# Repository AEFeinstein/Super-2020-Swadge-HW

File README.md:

# Super 2020 Swadge Hardware

This repo contains hardware files for the Super 2020 Barrel and Banana Swadges, as well as the Swadge Programmer and the Swadge Devkit. [KiCad](https://www.kicad-pcb.org/) is used to work with the project files. [Inkscape](https://inkscape.org/) is used to work with the SVG vectors.

The corresponding hardware repository for the Super 2020 Swadge Firmware [can be found here](https://github.com/AEFeinstein/Super-2020-Swadge-FW).

The Barrel and Banana use the same schematic:

View this project on [CADLAB.io](https://cadlab.io/project/1918).

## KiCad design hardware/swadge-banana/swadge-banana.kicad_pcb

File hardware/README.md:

More libraries can be found at https://github.com/kitspace/kicad_footprints

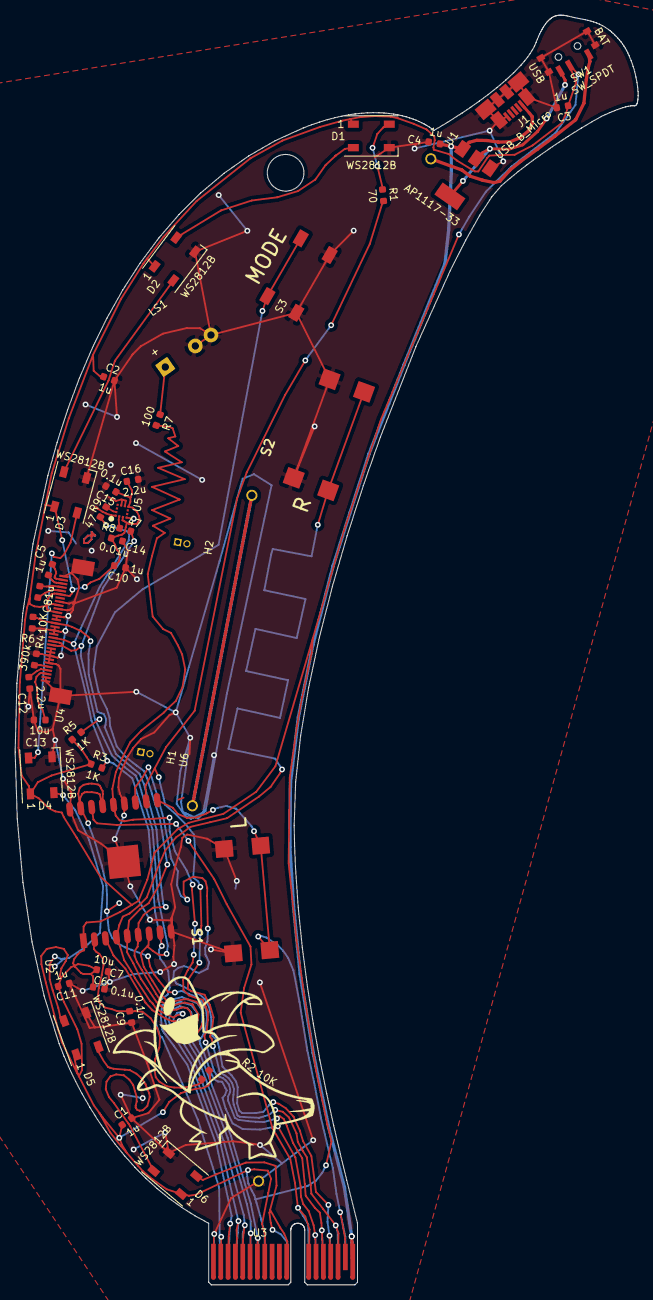
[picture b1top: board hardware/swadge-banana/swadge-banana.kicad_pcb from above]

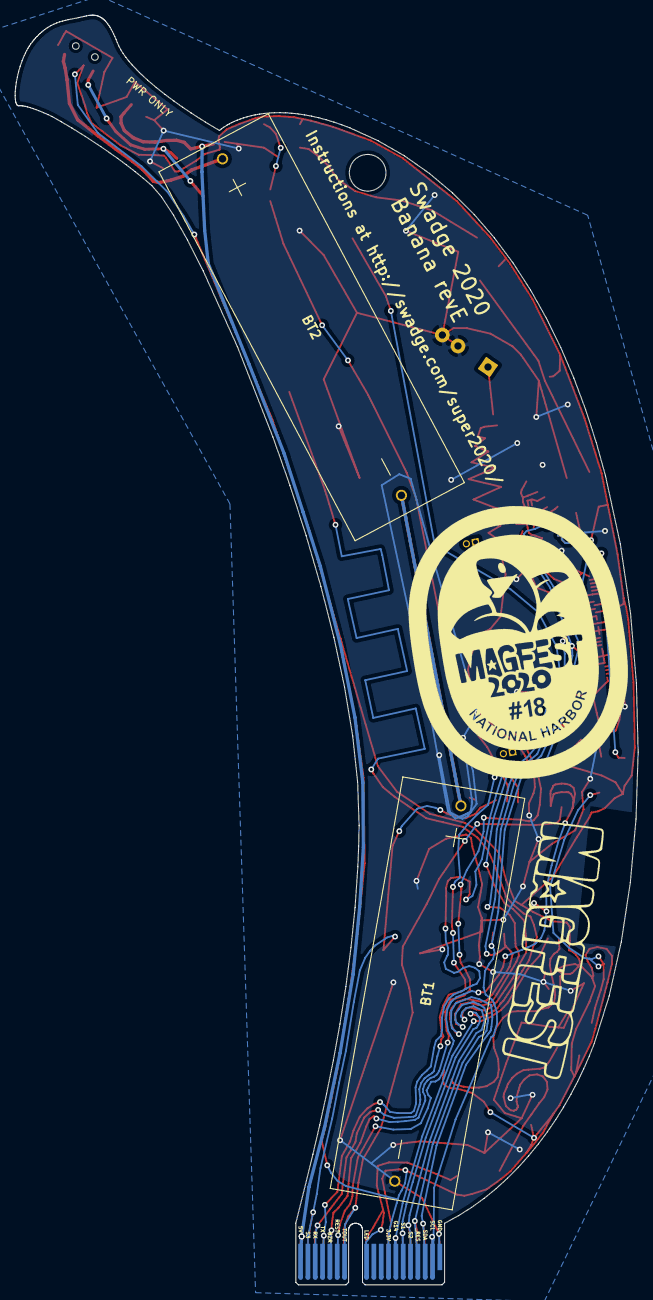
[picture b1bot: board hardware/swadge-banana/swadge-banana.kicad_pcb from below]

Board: 2 copper layers, 85.0 x 173.2 mm, 49 parts (3 on the bottom side), 36 nets.

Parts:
BT1, BT2: Battery; 2460
C1, C2, C3, C4, C5, C8, C10, C11: 1u; C_0603_1608Metric
C6, C13: 10u; C_0603_1608Metric
C7, C9, C15: 0.1u; C_0603_1608Metric
C12, C16: 2.2u; C_0603_1608Metric
C14: 0.01u; C_0603_1608Metric
D1, D2, D3, D4, D5, D6: WS2812B; LED_WS2812B_PLCC4_5.0x5.0mm_P3.2mm
H1: Headband
H2: Headband; NULL
J1: USB_B_Micro; USB_Micro-B_Molex_47346-0001
LS1: Speaker; Buzzer_12x9.5RM7.6
R1: 70; R_0603_1608Metric
R2, R6: 10K; R_0603_1608Metric
R3, R5: 1K; R_0603_1608Metric
R4: 390k; R_0603_1608Metric
R7: 100; R_0603_1608Metric
R8, R9: 47; R_0603_1608Metric
Ref**: Val**; bananaraptor_xl
Ref**#2: Val**; banana-label
S1, S2: B3FS-4002P; B3FS4002P
S3: 4-1437565-2; SW_4-1437565-2
SW1: SW_SPDT; SW_SPDT_PCM12
U1: AP1117-33; SOT-223-3_TabPin2
U2: ESP-13-WROOM-02D; ESP-13-WROOM-02
U3: BUS_PCIexpress
U4: OLED_CONNECTOR; ER-OLED0.96-1.3
U5: QMA6981; QMA6981_2
U6: OLED_DISPLAY; NULL

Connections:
+3V3: C1.1, C2.1, C3.1, C6.2, C7.2, C10.2, C11.2, C14.1, C15.1, C16.1, D1.1, D2.1, D3.1, D4.1, D5.1, D6.1, R2.1, R3.1, R5.1, SW1.2, U2.1, U3.A8, U3.B8, U4.6, U4.9, U4.11, U5.3, U5.7
+5V: C4.1, J1.1, U1.3, U3.A18, U3.B18
ADC_PIN: U2.16, U3.A12, U3.B12
AUD_PWR: U2.3, U3.A7, U3.B7
BZR: R7.2, U2.14, U3.A14, U3.B14
GND: BT1.2, C1.2, C2.2, C3.2, C4.2, C6.1, C7.1, C9.1, C10.1, C11.1, C12.1, C13.1, C14.2, C15.2, C16.2, D1.3, D2.3, D3.3, D4.3, D5.3, D6.3, J1.5, J1.6, LS1.2, R4.1, R6.1, S1.3, S1.4, S2.3, S2.4, S3.3, S3.4, SW1.4, SW1.5, SW1.6, SW1.7, U1.1, U2.9, U2.13, U2.18, U2.PAD, U3.A1, U3.B1, U4.1, U4.8, U4.10, U4.12, U4.13, U4.15, U4.16, U4.17, U4.21, U4.22, U4.23, U4.24, U4.25, U4.29, U4.30, U4.31, U5.1, U5.4, U5.8, U5.9
LED_OUT: D6.2, U3.A11, U3.B11
unnamed: BT1.1, BT2.2
unnamed: BT2.1, SW1.1
unnamed: C5.1, U4.2
unnamed: C5.2, U4.3
unnamed: C8.1, U4.4
unnamed: C8.2, U4.5
unnamed: C9.2, R2.2, U2.2
unnamed: C12.2, U4.27
unnamed: C13.2, U4.28
unnamed: D1.2, D2.4
unnamed: D1.4, R1.1
unnamed: D2.2, D3.4
unnamed: D3.2, D4.4
unnamed: D4.2, D5.4
unnamed: D5.2, D6.4
unnamed: LS1.1, R7.1
unnamed: R4.2, U4.26
unnamed: R8.1, U5.2
unnamed: R9.2, U5.12
unnamed: SW1.3, U1.2
REST: U2.15, U2.17, U3.A13, U3.B13
RX: R1.2, U2.11, U3.A16, U3.B16
SCL: R3.2, R9.1, U2.8, U3.A2, U3.B2, U4.18
SDA: R5.2, R8.2, U2.7, U3.A3, U3.B3, U4.19, U4.20
SW1: S2.1, S2.2, U2.4, U3.A6, U3.B6
SW2: S3.1, S3.2, U2.5, U3.A5, U3.B5
SW3: S1.1, S1.2, U2.10, U3.A17, U3.B17
TX: U2.12, U3.A15, U3.B15
_RES: R6.2, U2.6, U3.A4, U3.B4, U4.14

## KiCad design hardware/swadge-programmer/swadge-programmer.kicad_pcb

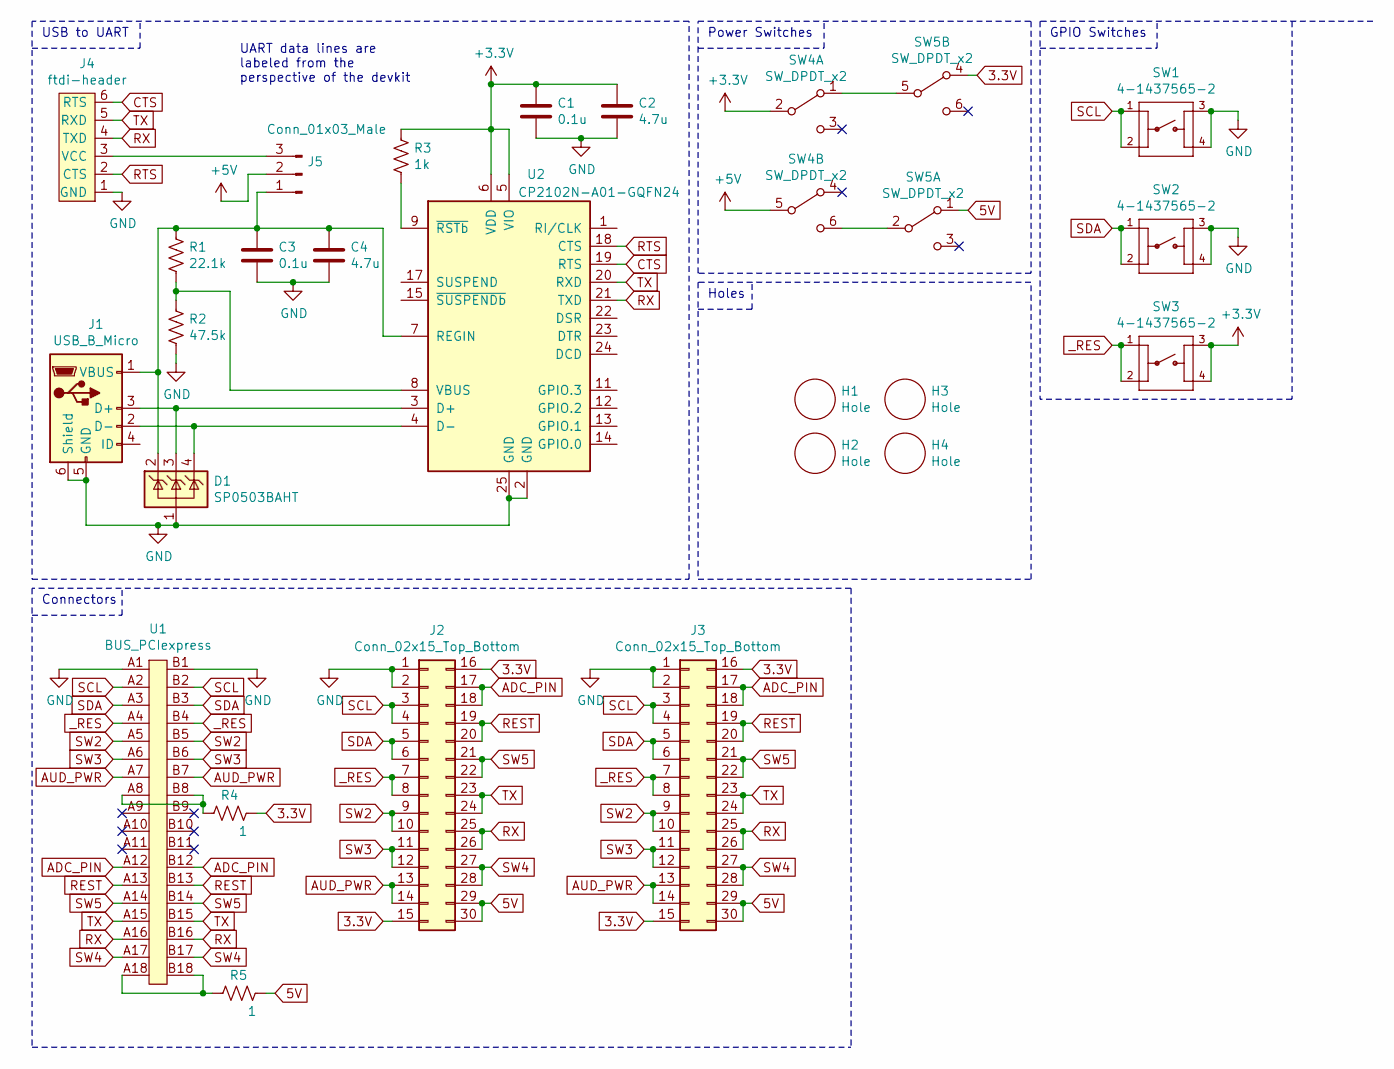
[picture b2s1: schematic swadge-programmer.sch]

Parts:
C1, C3: 0.1u; C_0603_1608Metric; Digikey 1276-1000-1-ND
C2, C4: 4.7u; C_0603_1608Metric; Digikey 1276-1045-1-ND
D1: SP0503BAHT; SOT-143; Digikey F2715CT-ND
H1, H2, H3, H4: Hole; Digikey 2042-1007-ND
J1: USB_B_Micro; USB_Micro-B_Molex_47346-0001; Digikey WM17141CT-ND
J2, J3: Conn_02x15_Top_Bottom; PinHeader_2x15_P2.54mm_Vertical; Digikey S2012EC-15-ND
J4: ftdi-header; Digikey n/a
J5: Conn_01x03_Male; PinHeader_1x03_P2.54mm_Vertical; Digikey 1849-1003-ND
R1: 22.1k; R_0603_1608Metric; Digikey RMCF0603FT22K1CT-ND
R2: 47.5k; R_0603_1608Metric; Digikey P47.5KHCT-ND
R3: 1k; R_0603_1608Metric; Digikey 311-1.00KHRCT-ND
R4, R5: 1; R_Axial_DIN0207_L6.3mm_D2.5mm_P10.16mm_Horizontal; Digikey RNF14FTD1R00CT-ND
SW1, SW2, SW3: 4-1437565-2; SW_4-1437565-2; MPN FSM4JSMATR; Digikey 450-1759-1-ND
SW4, SW5: SW_DPDT_x2; JS202011CQN; Digikey 401-2001-ND
U1: BUS_PCIexpress; 10018784-10210TLF; Digikey 609-2029-ND
U2: CP2102N-A01-GQFN24; QFN-24-1EP_4x4mm_P0.5mm_EP2.6x2.6mm; Digikey 336-4737-1-ND

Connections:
3.3V: J2.15, J2.16, J3.15, J3.16, R4.2, SW5.4 (A)
5V: J2.29, J2.30, J3.29, J3.30, R5.2, SW5.1 (A)
+3V3: C1.1, C2.1, R3.2, SW3.3, SW3.4, SW4.2 (B), U2.5 (VIO), U2.6 (VDD)
+5V: J5.2, SW4.5 (B)
ADC_PIN: J2.17, J2.18, J3.17, J3.18, U1.A12, U1.B12
AUD_PWR: J2.13, J2.14, J3.13, J3.14, U1.A7, U1.B7
CTS: J4.6 (RTS), U2.19 (RTS)
GND: C1.2, C2.2, C3.2, C4.2, D1.1 (A), J1.5 (GND), J1.6 (Shield), J2.1, J2.2, J3.1, J3.2, J4.1 (GND), R2.2, SW1.3, SW1.4, SW2.3, SW2.4, U1.A1, U1.B1, U2.2 (GND), U2.25 (GND)
unnamed: C3.1, C4.1, D1.2 (K), J1.1 (VBUS), J5.1, R1.1, U2.7 (REGIN)
unnamed: D1.3 (K), J1.3 (D+), U2.3 (D+)
unnamed: D1.4 (K), J1.2 (D-), U2.4 (D-)
unnamed: J4.3 (VCC), J5.3
unnamed: R1.2, R2.1, U2.8 (VBUS)
unnamed: R3.1, U2.9 (~RSTb)
unnamed: R4.1, U1.A8, U1.B8
unnamed: R5.1, U1.A18, U1.B18
unnamed: SW4.1 (A), SW5.5 (B)
unnamed: SW4.6 (C), SW5.2 (B)
REST: J2.19, J2.20, J3.19, J3.20, U1.A13, U1.B13
RTS: J4.2 (CTS), U2.18 (CTS)
RX: J2.25, J2.26, J3.25, J3.26, J4.4 (TXD), U1.A16, U1.B16, U2.21 (TXD)
SCL: J2.3, J2.4, J3.3, J3.4, SW1.1, SW1.2, U1.A2, U1.B2
SDA: J2.5, J2.6, J3.5, J3.6, SW2.1, SW2.2, U1.A3, U1.B3
SW2: J2.9, J2.10, J3.9, J3.10, U1.A5, U1.B5
SW3: J2.11, J2.12, J3.11, J3.12, U1.A6, U1.B6
SW4: J2.27, J2.28, J3.27, J3.28, U1.A17, U1.B17
SW5: J2.21, J2.22, J3.21, J3.22, U1.A14, U1.B14
TX: J2.23, J2.24, J3.23, J3.24, J4.5 (RXD), U1.A15, U1.B15, U2.20 (RXD)
_RES: J2.7, J2.8, J3.7, J3.8, SW3.1, SW3.2, U1.A4, U1.B4

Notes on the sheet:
Power Switches
GPIO Switches
USB to UART
Connectors
Holes
UART data lines are labeled from the perspective of the devkit

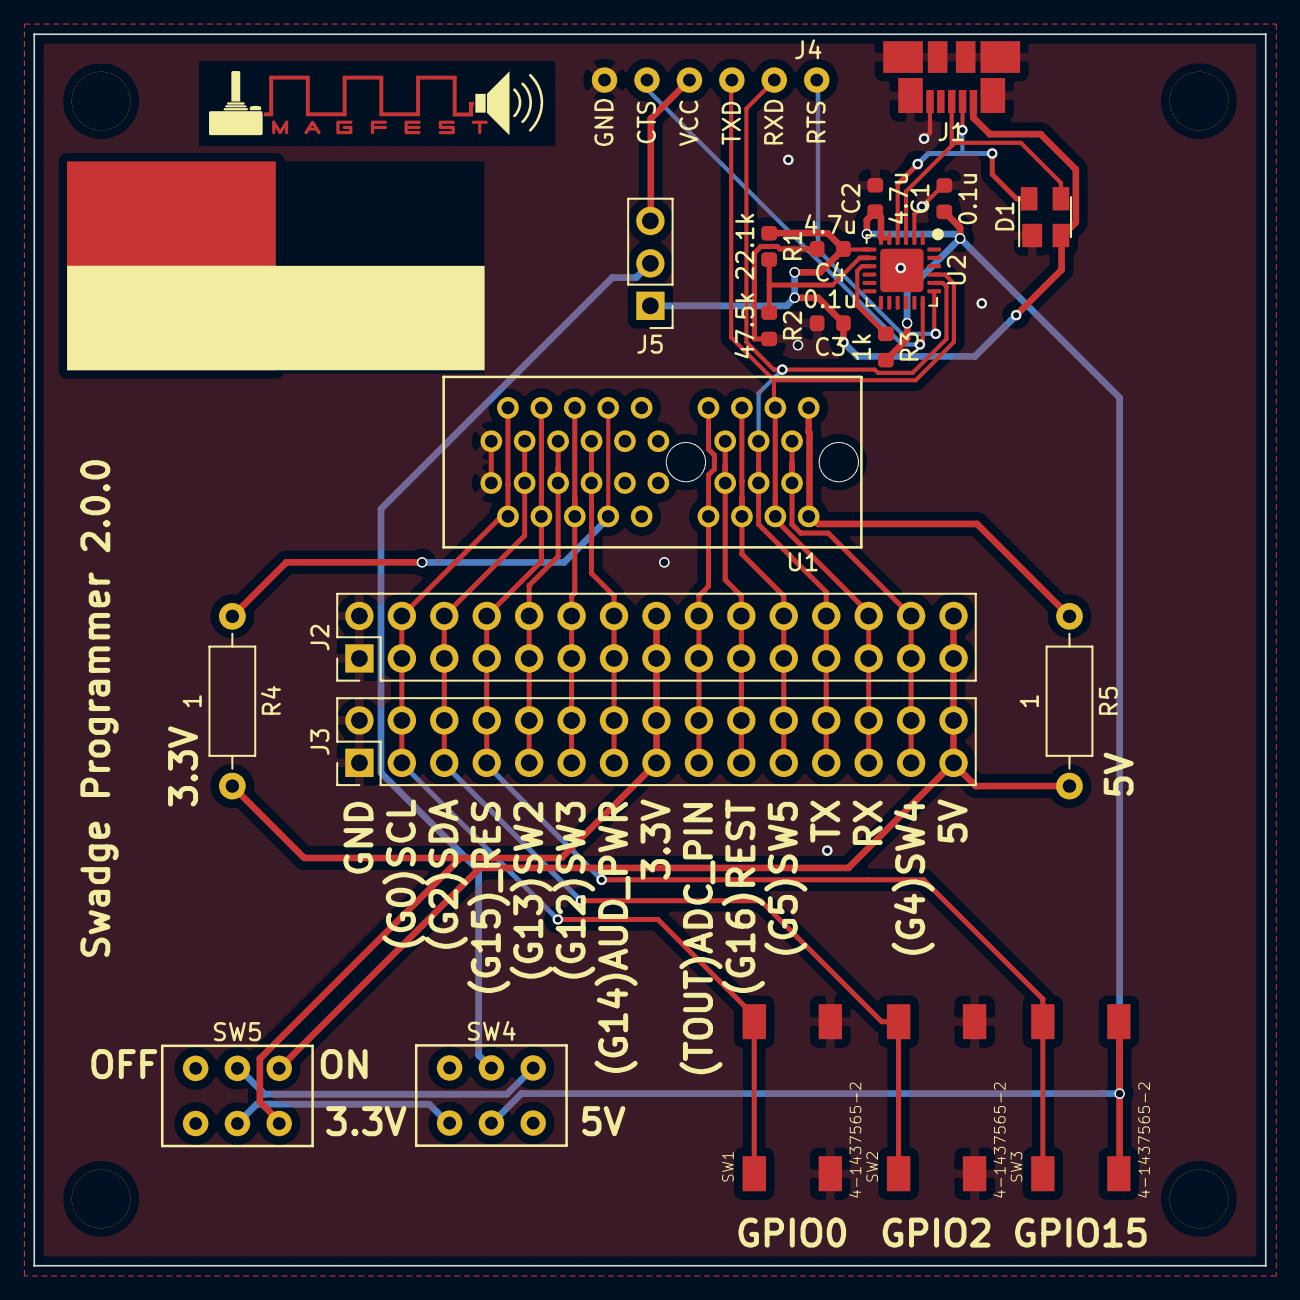
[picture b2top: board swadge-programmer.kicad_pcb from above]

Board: 2 copper layers, 73.7 x 73.7 mm, 28 parts (0 on the bottom side), 29 nets.

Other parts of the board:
svg2mod: G***; pcb_color_swatches
svg2mod#2: G***; MAGFEST_logo_centered_final

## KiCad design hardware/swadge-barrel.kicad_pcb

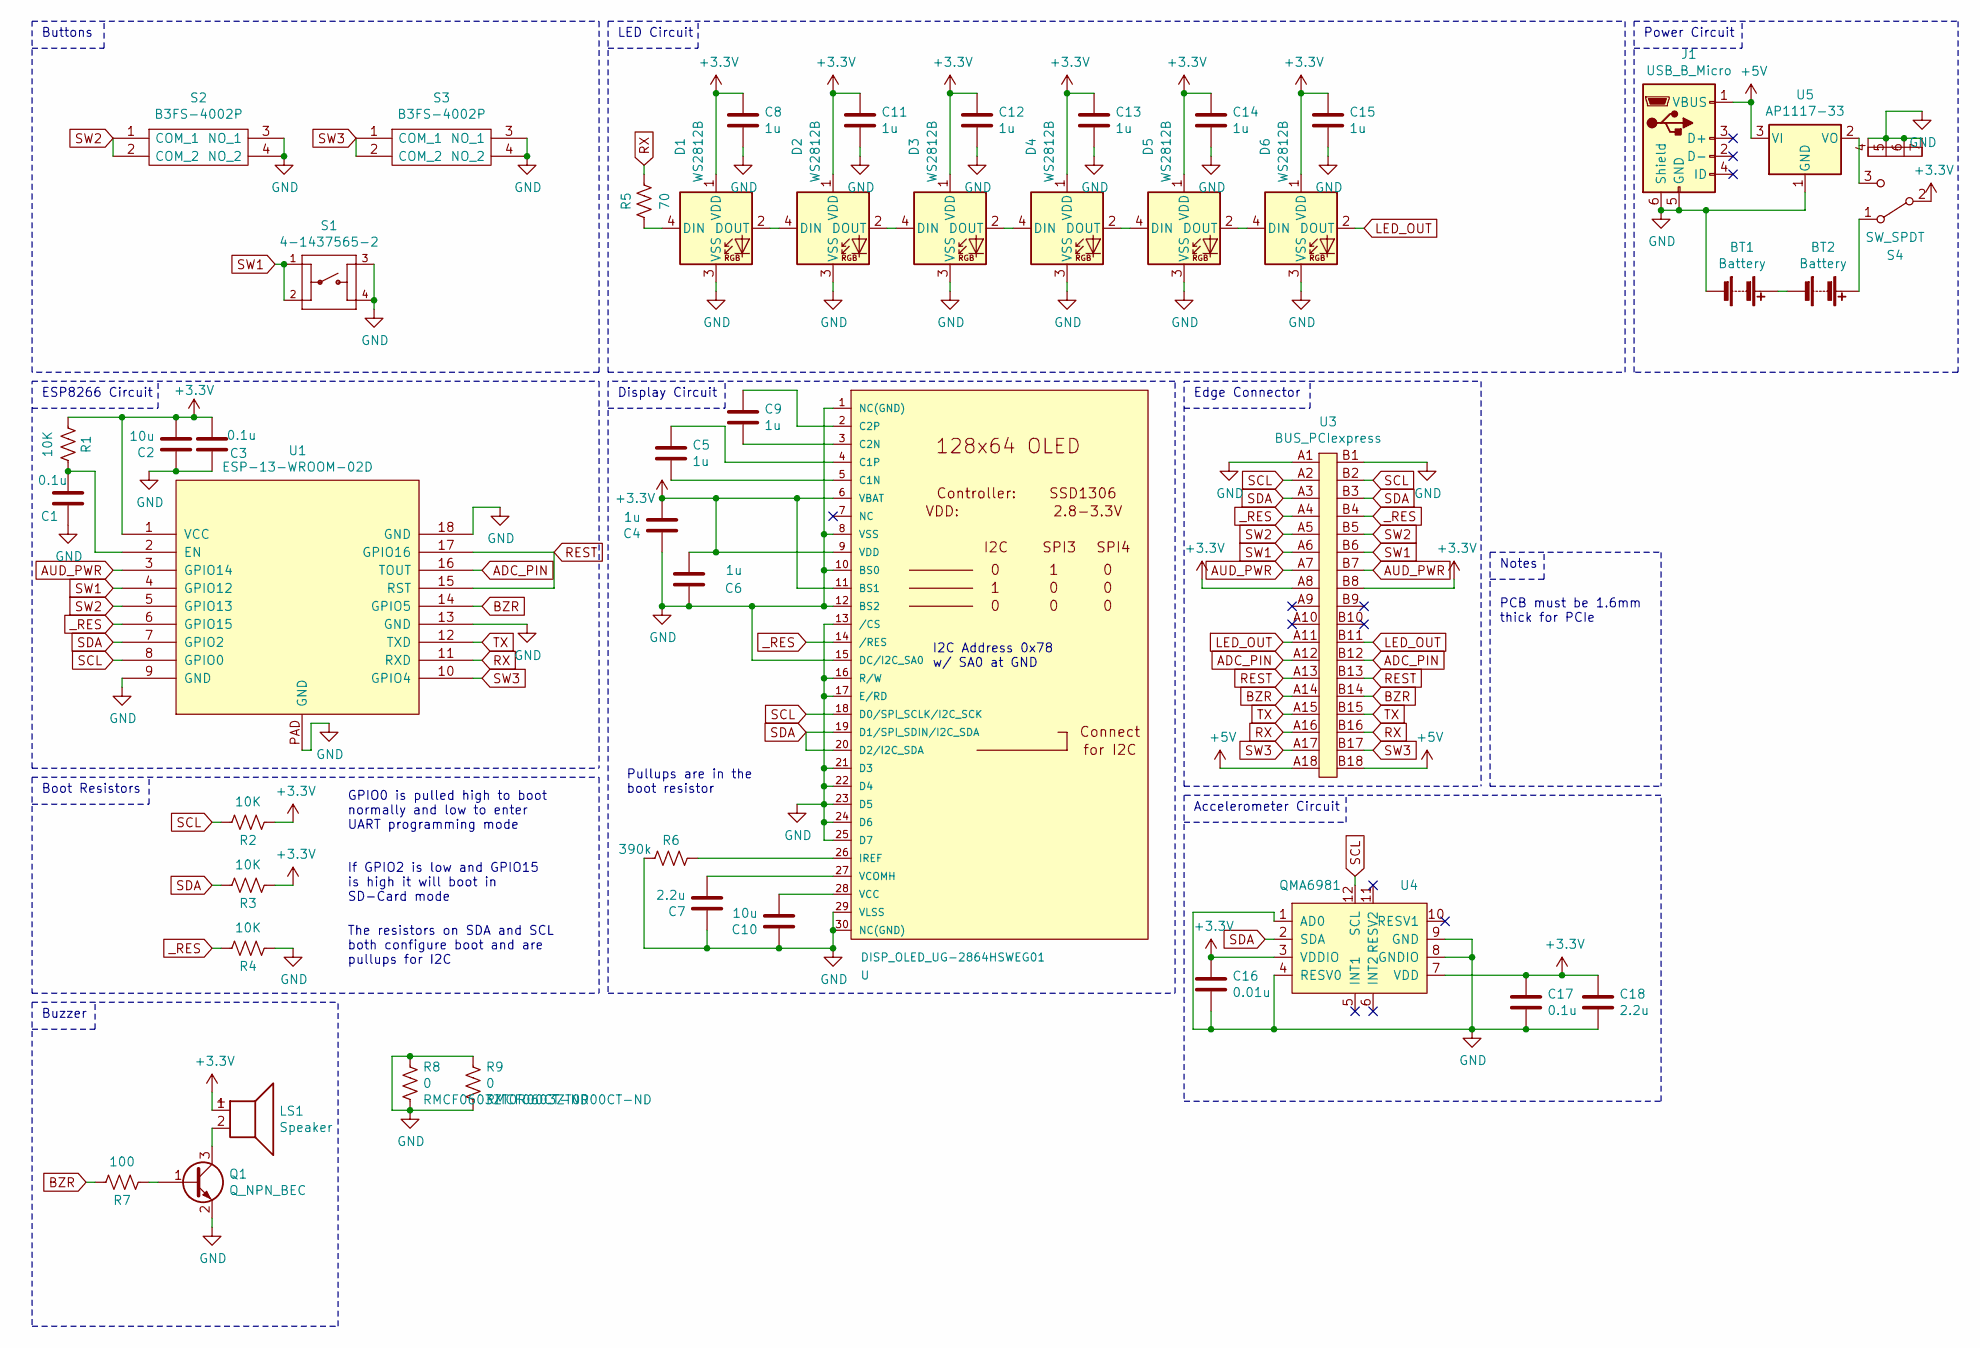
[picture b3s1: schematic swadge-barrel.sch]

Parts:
BT1, BT2: Battery; 2460; Digikey 36-2460-ND
C1, C3, C17: 0.1u; C_0603_1608Metric; Digikey 1276-1000-1-ND
C2, C10: 10u; C_0603_1608Metric; Digikey 490-10469-1-ND
C4, C5, C6, C9: 1u; C_1206_3216Metric; Digikey 1276-1036-1-ND
C7, C18: 2.2u; C_0603_1608Metric; Digikey 1276-1085-1-ND
C8, C11, C12, C13, C14, C15: 1u; C_0603_1608Metric; Digikey 1276-1036-1-ND
C16: 0.01u; C_0603_1608Metric; Digikey 1276-1000-1-ND
D1, D2, D3, D4, D5, D6: WS2812B; LED_WS2812B_PLCC4_5.0x5.0mm_P3.2mm; Digikey 1528-1104-ND
J1: USB_B_Micro; USB_Micro-B_Molex_47346-0001; Digikey WM17141CT-ND
LS1: Speaker; Speaker_9mm; Digikey LCSC Part #C96102
Q1: Q_NPN_BEC; SOT-23; Digikey BC848BLT3GOSTR-ND
R1, R2, R3, R4: 10K; R_0603_1608Metric; Digikey RNCP0603FTD10K0CT-ND
R5: 70; R_0603_1608Metric; Digikey 311-71.5HRCT-ND
R6: 390k; R_0603_1608Metric; Digikey 311-390KHRCT-ND
R7: 100; R_0603_1608Metric; Digikey RNCP0603FTD10K0CT-ND
R8, R9: 0; R_0603_1608Metric; Digikey RMCF0603ZT0R00CT-ND
S1: 4-1437565-2; SW_4-1437565-2; MPN FSM4JSMATR; Digikey 450-1759-1-ND
S2, S3: B3FS-4002P; B3FS4002P
S4: SW_SPDT; SW_SPDT_PCM12; Digikey 401-2016-1-ND
U: DISP_OLED_UG-2864HSWEG01; oled-flat_copy; Digikey 541-3485-ND
U1: ESP-13-WROOM-02D; ESP-13-WROOM-02; Digikey 1904-1021-1-ND
U3: BUS_PCIexpress; Digikey n/a
U4: QMA6981; Digikey LCSC Part #C310611
U5: AP1117-33; SOT-223-3_TabPin2; Digikey AP2114H-3.3TRG1DICT-ND

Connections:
+3V3: C2.2, C3.2, C4.2, C6.2, C8.1, C11.1, C12.1, C13.1, C14.1, C15.1, C16.1, C17.1, C18.1, D1.1 (VDD), D2.1 (VDD), D3.1 (VDD), D4.1 (VDD), D5.1 (VDD), D6.1 (VDD), LS1.1, R1.1, R2.1, R3.1, S4.2 (B), U.6 (VBAT), U.9 (VDD), U.11 (BS1), U1.1 (VCC), U3.A8, U3.B8, U4.3 (VDDIO), U4.7 (VDD); also elsewhere on the board
+5V: J1.1 (VBUS), U3.A18, U3.B18, U5.3 (VI)
ADC_PIN: U1.16 (TOUT), U3.A12, U3.B12
AUD_PWR: U1.3 (GPIO14), U3.A7, U3.B7
BZR: R7.2, U1.14 (GPIO5), U3.A14, U3.B14
GND: BT1.2 (-), C1.1, C2.1, C3.1, C4.1, C6.1, C7.1, C8.2, C10.1, C11.2, C12.2, C13.2, C14.2, C15.2, C16.2, C17.2, C18.2, D1.3 (VSS), D2.3 (VSS), D3.3 (VSS), D4.3 (VSS), D5.3 (VSS), D6.3 (VSS), J1.5 (GND), J1.6 (Shield), Q1.2 (E), R4.1, R6.1, R8.1, R8.2, R9.1, R9.2, S1.3, S1.4, S2.3 (NO_1), S2.4 (NO_2), S3.3 (NO_1), S3.4 (NO_2), S4.4 (D), S4.5 (E), S4.6 (F), S4.7 (G), U.1 (NC(GND)), U.8 (VSS), U.10 (BS0), U.12 (BS2), U.13 (/CS), U.15 (DC/I2C_SA0), U.16 (R/W), U.17 (E/RD), U.21 (D3), U.22 (D4), U.23 (D5), U.24 (D6), U.25 (D7), U.29 (VLSS), U.30 (NC(GND)), U1.9 (GND), U1.13 (GND), U1.18 (GND), U1.PAD (GND), U3.A1, U3.B1, U4.1 (AD0), U4.4 (RESV0), U4.8 (GNDIO), U4.9 (GND), U5.1 (GND); also elsewhere on the board
LED_OUT: D6.2 (DOUT), U3.A11, U3.B11
unnamed: BT1.1 (+), BT2.2 (-)
unnamed 8: BT2.1 (+), S4.1 (A); also elsewhere on the board
unnamed: C1.2, R1.2, U1.2 (EN)
unnamed 10: C5.1, U.4 (C1P); also elsewhere on the board
unnamed 11: C5.2, U.5 (C1N); also elsewhere on the board
unnamed 12: C7.2, U.27 (VCOMH); also elsewhere on the board
unnamed 13: C9.1, U.2 (C2P); also elsewhere on the board
unnamed 14: C9.2, U.3 (C2N); also elsewhere on the board
unnamed 15: C10.2, U.28 (VCC); also elsewhere on the board
unnamed: D1.2 (DOUT), D2.4 (DIN)
unnamed: D1.4 (DIN), R5.1
unnamed: D2.2 (DOUT), D3.4 (DIN)
unnamed: D3.2 (DOUT), D4.4 (DIN)
unnamed: D4.2 (DOUT), D5.4 (DIN)
unnamed: D5.2 (DOUT), D6.4 (DIN)
unnamed: LS1.2, Q1.3 (C)
unnamed: Q1.1 (B), R7.1
unnamed 24: R6.2, U.26 (IREF); also elsewhere on the board
unnamed 25: S4.3 (C), U5.2 (VO); also elsewhere on the board
REST: U1.15 (RST), U1.17 (GPIO16), U3.A13, U3.B13
RX: R5.2, U1.11 (RXD), U3.A16, U3.B16
SCL: R2.2, U.18 (D0/SPI_SCLK/I2C_SCK), U1.8 (GPIO0), U3.A2, U3.B2, U4.12 (SCL); also elsewhere on the board
SDA: R3.2, U.19 (D1/SPI_SDIN/I2C_SDA), U.20 (D2/I2C_SDA), U1.7 (GPIO2), U3.A3, U3.B3, U4.2 (SDA); also elsewhere on the board
SW1: S1.1, S1.2, U1.4 (GPIO12), U3.A6, U3.B6
SW2: S2.1 (COM_1), S2.2 (COM_2), U1.5 (GPIO13), U3.A5, U3.B5
SW3: S3.1 (COM_1), S3.2 (COM_2), U1.10 (GPIO4), U3.A17, U3.B17
TX: U1.12 (TXD), U3.A15, U3.B15
_RES: R4.2, U.14 (/RES), U1.6 (GPIO15), U3.A4, U3.B4; also elsewhere on the board

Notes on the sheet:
LED Circuit
ESP8266 Circuit
GPIO0 is pulled high to boot normally and low to enter UART programming mode
If GPIO2 is low and GPIO15 is high it will boot in SD-Card mode
Boot Resistors
Power Circuit
Buttons
Edge Connector
Pullups are in the boot resistor
I2C Address 0x78 w/ SA0 at GND
Display Circuit
PCB must be 1.6mm thick for PCIe
Notes
The resistors on SDA and SCL both configure boot and are pullups for I2C
Accelerometer Circuit
Buzzer

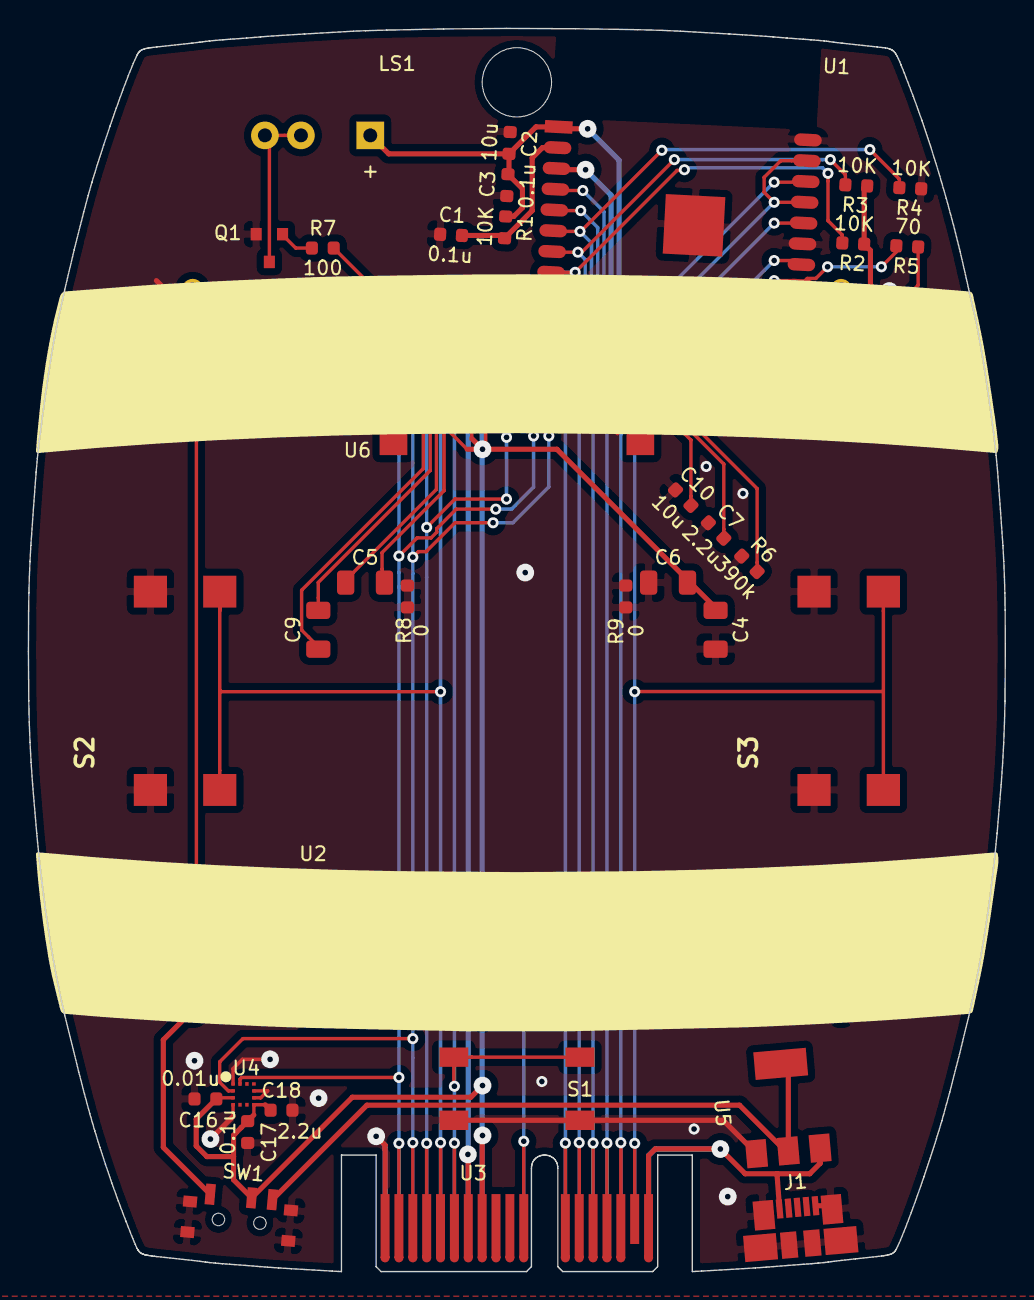
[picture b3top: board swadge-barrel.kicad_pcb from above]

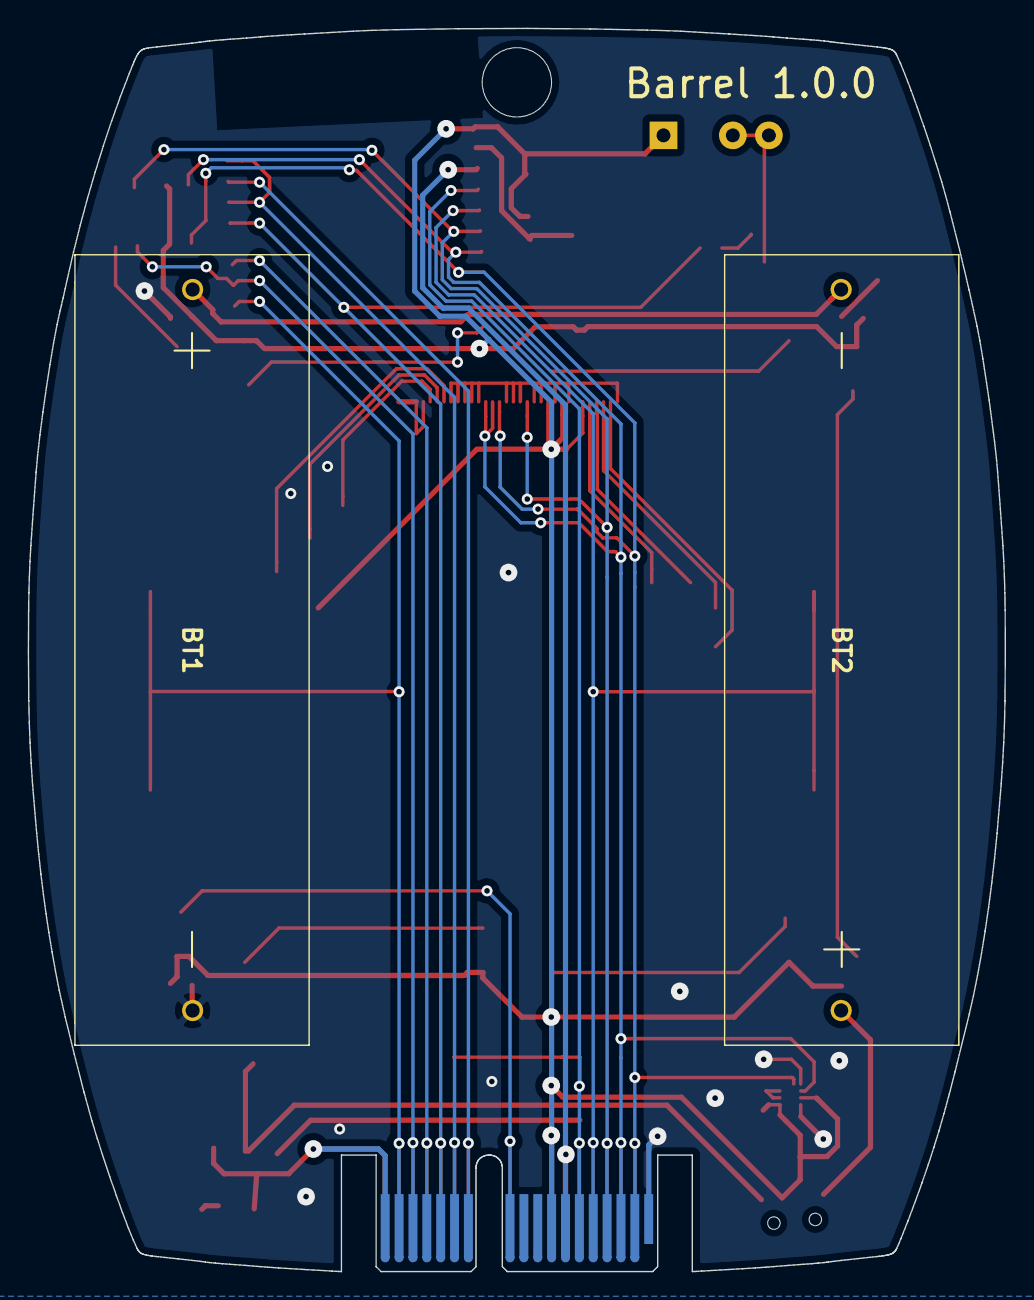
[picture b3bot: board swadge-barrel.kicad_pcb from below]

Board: 2 copper layers, 70.4 x 89.6 mm, 48 parts (2 on the bottom side), 35 nets.

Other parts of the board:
SW1: SW_SPDT; SW_SPDT_PCM12
U2: OLED_DISPLAY; NULL
U6: OLED_CONNECTOR; oled-flat_copy

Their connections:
+3V3: SW1.2, U6.6, U6.9, U6.11; also elsewhere on the board
GND: SW1.4, SW1.5, SW1.6, SW1.7, U6.1, U6.8, U6.10, U6.12, U6.13, U6.15, U6.16, U6.17, U6.21, U6.22, U6.23, U6.24, U6.25, U6.29, U6.30; also elsewhere on the board
unnamed 8: SW1.1; also elsewhere on the board
unnamed 10: U6.4; also elsewhere on the board
unnamed 11: U6.5; also elsewhere on the board
unnamed 12: U6.27; also elsewhere on the board
unnamed 13: U6.2; also elsewhere on the board
unnamed 14: U6.3; also elsewhere on the board
unnamed 15: U6.28; also elsewhere on the board
unnamed 24: U6.26; also elsewhere on the board
unnamed 25: SW1.3; also elsewhere on the board
SCL: U6.18; also elsewhere on the board
SDA: U6.19, U6.20; also elsewhere on the board
_RES: U6.14; also elsewhere on the board

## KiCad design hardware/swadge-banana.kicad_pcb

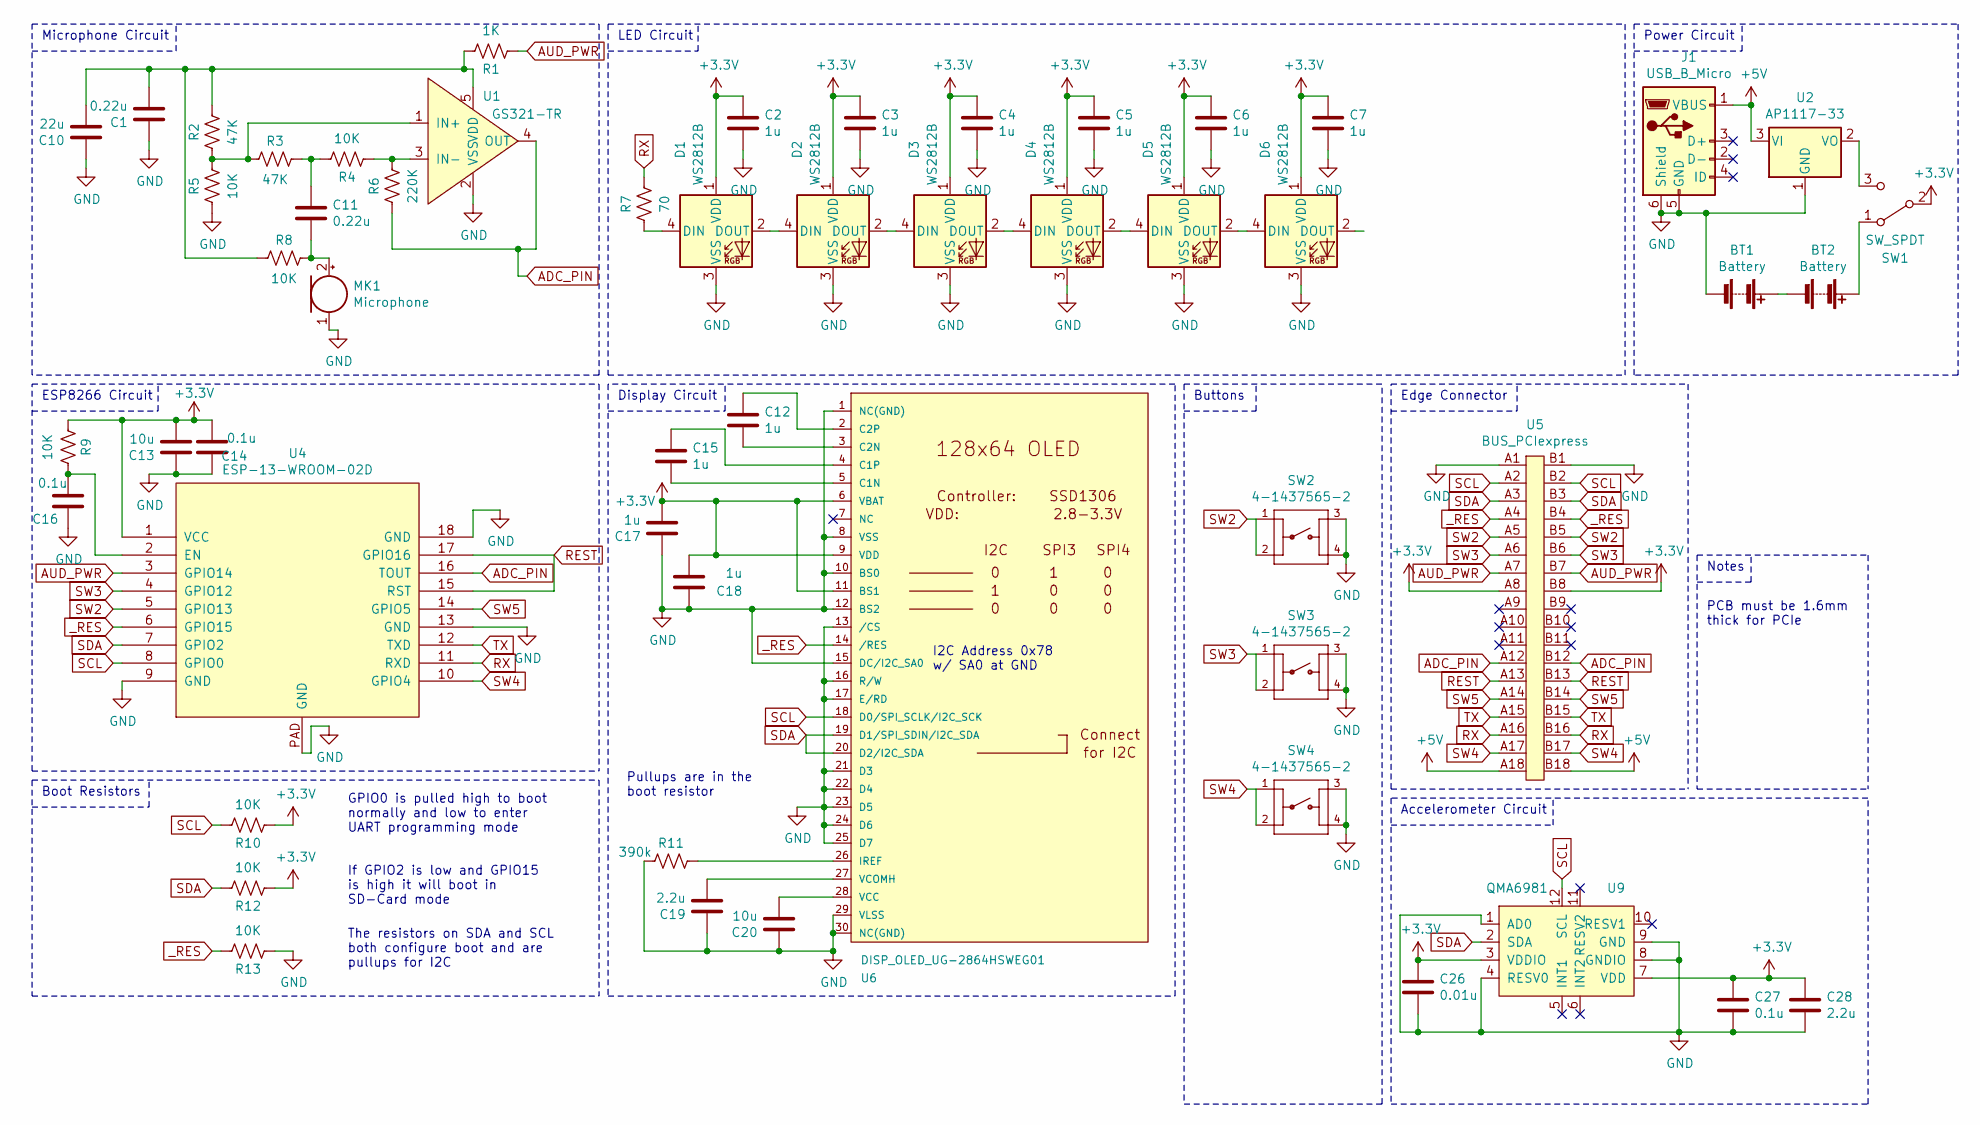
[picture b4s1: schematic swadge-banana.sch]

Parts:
BT1, BT2: Battery; 2460; Digikey 36-2460-ND
C1, C11: 0.22u; C_0603_1608Metric; Digikey 587-1249-1-ND
C2, C3, C4, C5, C6, C7, C12, C15, C17, C18: 1u; C_0603_1608Metric; Digikey 1276-1036-1-ND
C10: 22u; C_0603_1608Metric; Digikey 490-7611-1-ND
C13, C20: 10u; C_0603_1608Metric; Digikey 490-10469-1-ND
C14, C16, C27: 0.1u; C_0603_1608Metric; Digikey 1276-1000-1-ND
C19: 2.2u; C_0603_1608Metric; Digikey 1276-1085-1-ND
C26: 0.01u; C_0603_1608Metric; Digikey 1276-1000-1-ND
C28: 2.2u; C_0603_1608Metric; Digikey 1276-1000-1-ND
D1, D2, D3, D4, D5, D6: WS2812B; LED_WS2812B_PLCC4_5.0x5.0mm_P3.2mm; Digikey 1528-1104-ND
J1: USB_B_Micro; USB_Micro-B_Molex_47346-0001; Digikey WM17141CT-ND
MK1: Microphone; CMA-4544PF-W; Digikey 102-1721-ND
R1: 1K; R_0603_1608Metric; Digikey 311-1.00KHRCT-ND
R2, R3: 47K; R_0603_1608Metric; Digikey 311-47KGRCT-ND
R4, R5, R8, R9, R10, R12, R13: 10K; R_0603_1608Metric; Digikey RNCP0603FTD10K0CT-ND
R6: 220K; R_0603_1608Metric; Digikey A129716CT-ND
R7: 70; R_0603_1608Metric; Digikey 311-71.5HRCT-ND
R11: 390k; R_0603_1608Metric; Digikey 311-390KHRCT-ND
SW1: SW_SPDT; SW_SPDT_PCM12; Digikey 401-2016-1-ND
SW2, SW3, SW4: 4-1437565-2; SW_4-1437565-2; MPN FSM4JSMATR; Digikey 450-1759-1-ND
U1: GS321-TR; SOT-23-5; Digikey MCP6001UT-I/OTCT-ND
U2: AP1117-33; SOT-223-3_TabPin2; Digikey AP2114H-3.3TRG1DICT-ND
U4: ESP-13-WROOM-02D; ESP-13-WROOM-02; Digikey 1904-1021-1-ND
U5: BUS_PCIexpress; Digikey n/a
U6: DISP_OLED_UG-2864HSWEG01; microbuilder-UG-2864HSWEG01_0.96IN_WRAPAROUND; Digikey 541-3486-ND
U9: QMA6981; Digikey LCSC Part #C310611

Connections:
+3V3: C2.1, C3.1, C4.1, C5.1, C6.1, C7.1, C13.2, C14.2, C17.2, C18.2, C26.1, C27.1, C28.1, D1.1 (VDD), D2.1 (VDD), D3.1 (VDD), D4.1 (VDD), D5.1 (VDD), D6.1 (VDD), R9.1, R10.1, R12.1, SW1.2 (B), U4.1 (VCC), U5.A8, U5.B8, U6.6 (VBAT), U6.9 (VDD), U6.11 (BS1), U9.3 (VDDIO), U9.7 (VDD)
+5V: J1.1 (VBUS), U2.3 (VI), U5.A18, U5.B18
ADC_PIN: R6.1, U1.4 (OUT), U4.16 (TOUT), U5.A12, U5.B12
AUD_PWR: R1.1, U4.3 (GPIO14), U5.A7, U5.B7
GND: BT1.2 (-), C1.1, C2.2, C3.2, C4.2, C5.2, C6.2, C7.2, C10.1, C13.1, C14.1, C16.1, C17.1, C18.1, C19.1, C20.1, C26.2, C27.2, C28.2, D1.3 (VSS), D2.3 (VSS), D3.3 (VSS), D4.3 (VSS), D5.3 (VSS), D6.3 (VSS), J1.5 (GND), J1.6 (Shield), MK1.1 (-), R5.1, R11.1, R13.1, SW2.3, SW2.4, SW3.3, SW3.4, SW4.3, SW4.4, U1.2 (VSS), U2.1 (GND), U4.9 (GND), U4.13 (GND), U4.18 (GND), U4.PAD (GND), U5.A1, U5.B1, U6.1 (NC(GND)), U6.8 (VSS), U6.10 (BS0), U6.12 (BS2), U6.13 (/CS), U6.15 (DC/I2C_SA0), U6.16 (R/W), U6.17 (E/RD), U6.21 (D3), U6.22 (D4), U6.23 (D5), U6.24 (D6), U6.25 (D7), U6.29 (VLSS), U6.30 (NC(GND)), U9.1 (AD0), U9.4 (RESV0), U9.8 (GNDIO), U9.9 (GND)
unnamed: BT1.1 (+), BT2.2 (-)
unnamed: BT2.1 (+), SW1.1 (A)
unnamed: C1.2, C10.2, R1.2, R2.2, R8.1, U1.5 (VDD)
unnamed: C11.1, R3.2, R4.2
unnamed: C11.2, MK1.2 (+), R8.2
unnamed: C12.1, U6.2 (C2P)
unnamed: C12.2, U6.3 (C2N)
unnamed: C15.1, U6.4 (C1P)
unnamed: C15.2, U6.5 (C1N)
unnamed: C16.2, R9.2, U4.2 (EN)
unnamed: C19.2, U6.27 (VCOMH)
unnamed: C20.2, U6.28 (VCC)
unnamed: D1.2 (DOUT), D2.4 (DIN)
unnamed: D1.4 (DIN), R7.1
unnamed: D2.2 (DOUT), D3.4 (DIN)
unnamed: D3.2 (DOUT), D4.4 (DIN)
unnamed: D4.2 (DOUT), D5.4 (DIN)
unnamed: D5.2 (DOUT), D6.4 (DIN)
unnamed: R2.1, R3.1, R5.2, U1.1 (IN+)
unnamed: R4.1, R6.2, U1.3 (IN-)
unnamed: R11.2, U6.26 (IREF)
unnamed: SW1.3 (C), U2.2 (VO)
REST: U4.15 (RST), U4.17 (GPIO16), U5.A13, U5.B13
RX: R7.2, U4.11 (RXD), U5.A16, U5.B16
SCL: R10.2, U4.8 (GPIO0), U5.A2, U5.B2, U6.18 (D0/SPI_SCLK/I2C_SCK), U9.12 (SCL)
SDA: R12.2, U4.7 (GPIO2), U5.A3, U5.B3, U6.19 (D1/SPI_SDIN/I2C_SDA), U6.20 (D2/I2C_SDA), U9.2 (SDA)
SW2: SW2.1, SW2.2, U4.5 (GPIO13), U5.A5, U5.B5
SW3: SW3.1, SW3.2, U4.4 (GPIO12), U5.A6, U5.B6
SW4: SW4.1, SW4.2, U4.10 (GPIO4), U5.A17, U5.B17
SW5: U4.14 (GPIO5), U5.A14, U5.B14
TX: U4.12 (TXD), U5.A15, U5.B15
_RES: R13.2, U4.6 (GPIO15), U5.A4, U5.B4, U6.14 (/RES)

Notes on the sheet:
Microphone Circuit
LED Circuit
ESP8266 Circuit
GPIO0 is pulled high to boot normally and low to enter UART programming mode
If GPIO2 is low and GPIO15 is high it will boot in SD-Card mode
Boot Resistors
Power Circuit
Buttons
Edge Connector
Pullups are in the boot resistor
I2C Address 0x78 w/ SA0 at GND
Display Circuit
PCB must be 1.6mm thick for PCIe
Notes
The resistors on SDA and SCL both configure boot and are pullups for I2C
Accelerometer Circuit

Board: 2 copper layers, 54 parts (2 on the bottom side), 36 nets, no tracks yet.

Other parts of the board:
Ref**: Val**; banana
